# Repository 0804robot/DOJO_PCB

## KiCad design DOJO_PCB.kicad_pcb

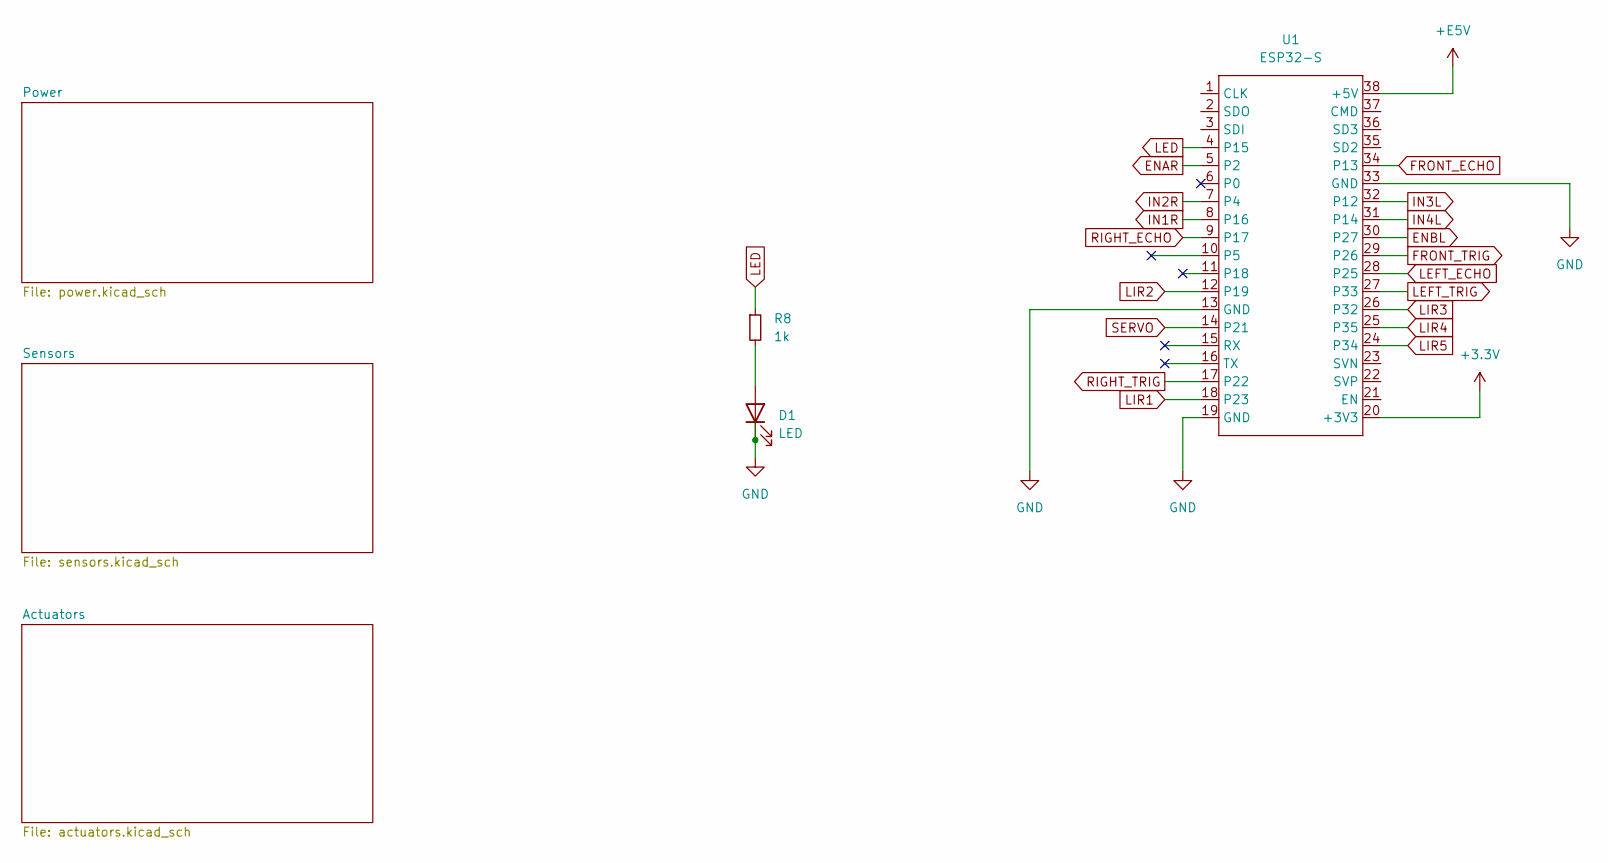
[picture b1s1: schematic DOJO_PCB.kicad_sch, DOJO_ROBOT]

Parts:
D1: LED; PinHeader_1x02_P2.54mm_Vertical
R8: 1k; R_Axial_DIN0207_L6.3mm_D2.5mm_P10.16mm_Horizontal
U1: ESP32-S

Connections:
+3.3V: U1.20 (+3V3); also elsewhere on the board
+E5V: U1.38 (+5V); also elsewhere on the board
ENAR: U1.5 (P2); also elsewhere on the board
ENBL: U1.30 (P27); also elsewhere on the board
FRONT_ECHO: U1.34 (P13); also elsewhere on the board
FRONT_TRIG: U1.29 (P26); also elsewhere on the board
GND: D1.1 (K), U1.13 (GND), U1.19 (GND), U1.33 (GND); also elsewhere on the board
IN1R: U1.8 (P16); also elsewhere on the board
IN2R: U1.7 (P4); also elsewhere on the board
IN3L: U1.32 (P12)
IN4L: U1.31 (P14)
LED: R8.1, U1.4 (P15)
LEFT_ECHO: U1.28 (P25); also elsewhere on the board
LEFT_TRIG: U1.27 (P33); also elsewhere on the board
LIR1: U1.18 (P23); also elsewhere on the board
LIR2: U1.12 (P19); also elsewhere on the board
LIR3: U1.26 (P32); also elsewhere on the board
LIR4: U1.25 (P35); also elsewhere on the board
LIR5: U1.24 (P34); also elsewhere on the board
unnamed: D1.2 (A), R8.2
RIGHT_ECHO: U1.9 (P17); also elsewhere on the board
RIGHT_TRIG: U1.17 (P22); also elsewhere on the board
SERVO: U1.14 (P21); also elsewhere on the board

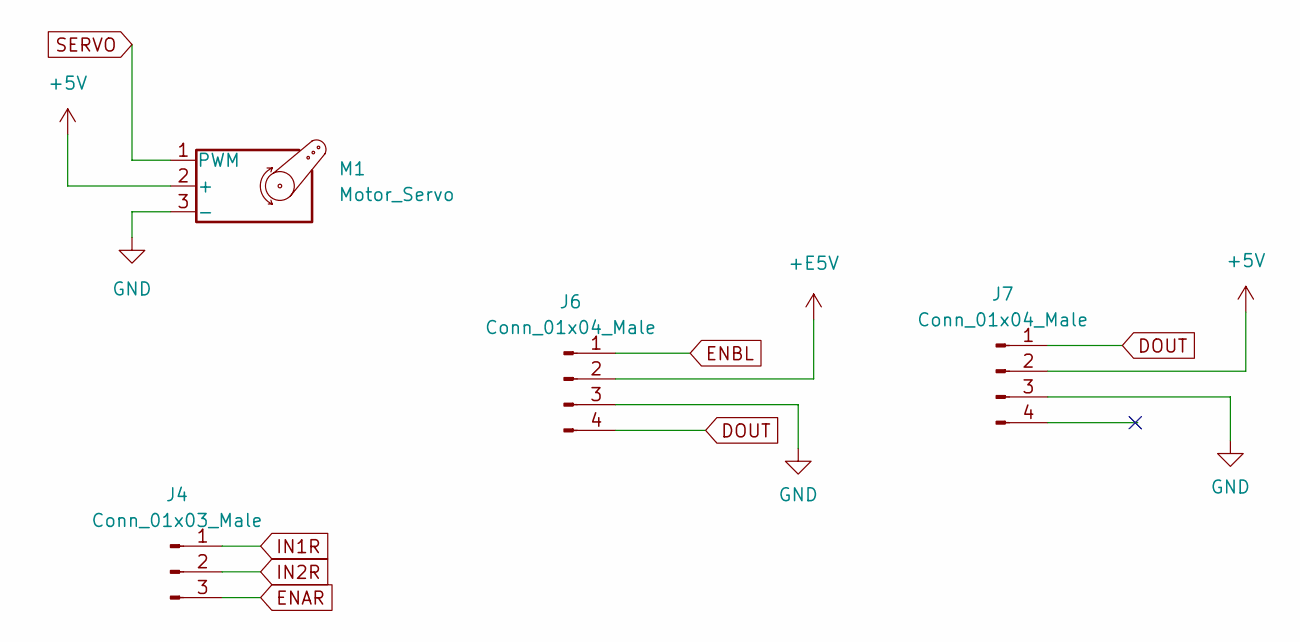
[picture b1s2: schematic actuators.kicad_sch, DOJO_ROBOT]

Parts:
J4: Conn_01x03_Male; Molex_KK-254_AE-6410-03A_1x03_P2.54mm_Vertical
J6, J7: Conn_01x04_Male; PinHeader_1x04_P2.54mm_Vertical
M1: Motor_Servo; Molex_KK-254_AE-6410-03A_1x03_P2.54mm_Vertical

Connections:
+5V: J6.2, J7.2, M1.2 (+); also elsewhere on the board
DOUT: J6.4, J7.1
ENAR: J4.3; also elsewhere on the board
ENBL: J6.1; also elsewhere on the board
GND: J6.3, J7.3, M1.3 (-); also elsewhere on the board
IN1R: J4.1; also elsewhere on the board
IN2R: J4.2; also elsewhere on the board
SERVO: M1.1 (PWM); also elsewhere on the board

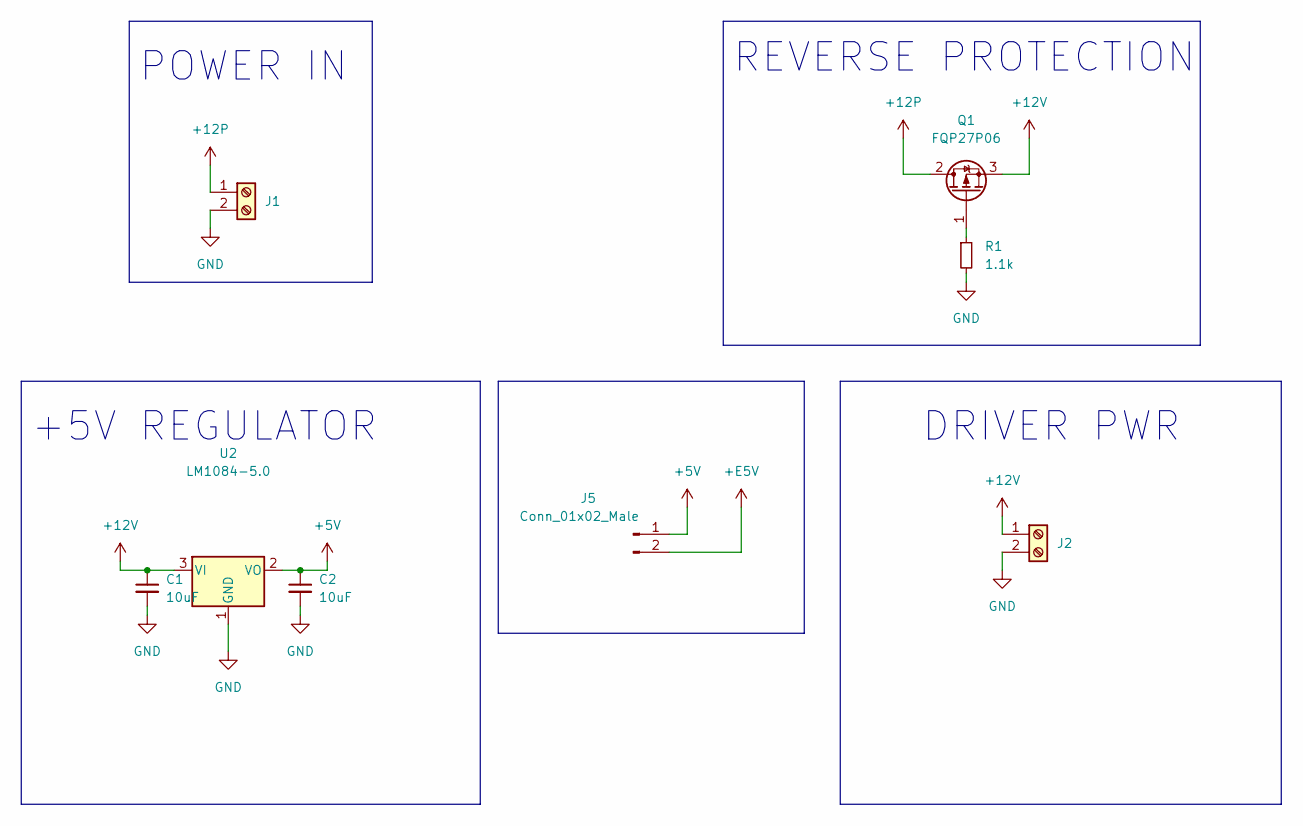
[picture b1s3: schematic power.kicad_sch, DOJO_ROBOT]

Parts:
C1, C2: 10uF; CP_Radial_D5.0mm_P2.50mm
J1, J2: Screw_Terminal_01x02; TerminalBlock_Phoenix_MKDS-1,5-2-5.08_1x02_P5.08mm_Horizont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
J5: Conn_01x02_Male; PinHeader_1x02_P2.54mm_Vertical
Q1: FQP27P06; TO-220-3_Vertical
R1: 1.1k; R_Axial_DIN0207_L6.3mm_D2.5mm_P10.16mm_Horizontal
U2: LM1084-5.0; TO-220-3_Vertical

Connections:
+5V: C2.1, J5.1, U2.2 (VO); also elsewhere on the board
+12P: J1.1, Q1.2 (D)
+12V: C1.1, J2.1, Q1.3 (S), U2.3 (VI)
+E5V: J5.2; also elsewhere on the board
GND: C1.2, C2.2, J1.2, J2.2, R1.2, U2.1 (GND); also elsewhere on the board
unnamed: Q1.1 (G), R1.1

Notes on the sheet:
+5V REGULATOR
REVERSE PROTECTION
DRIVER PWR
POWER IN

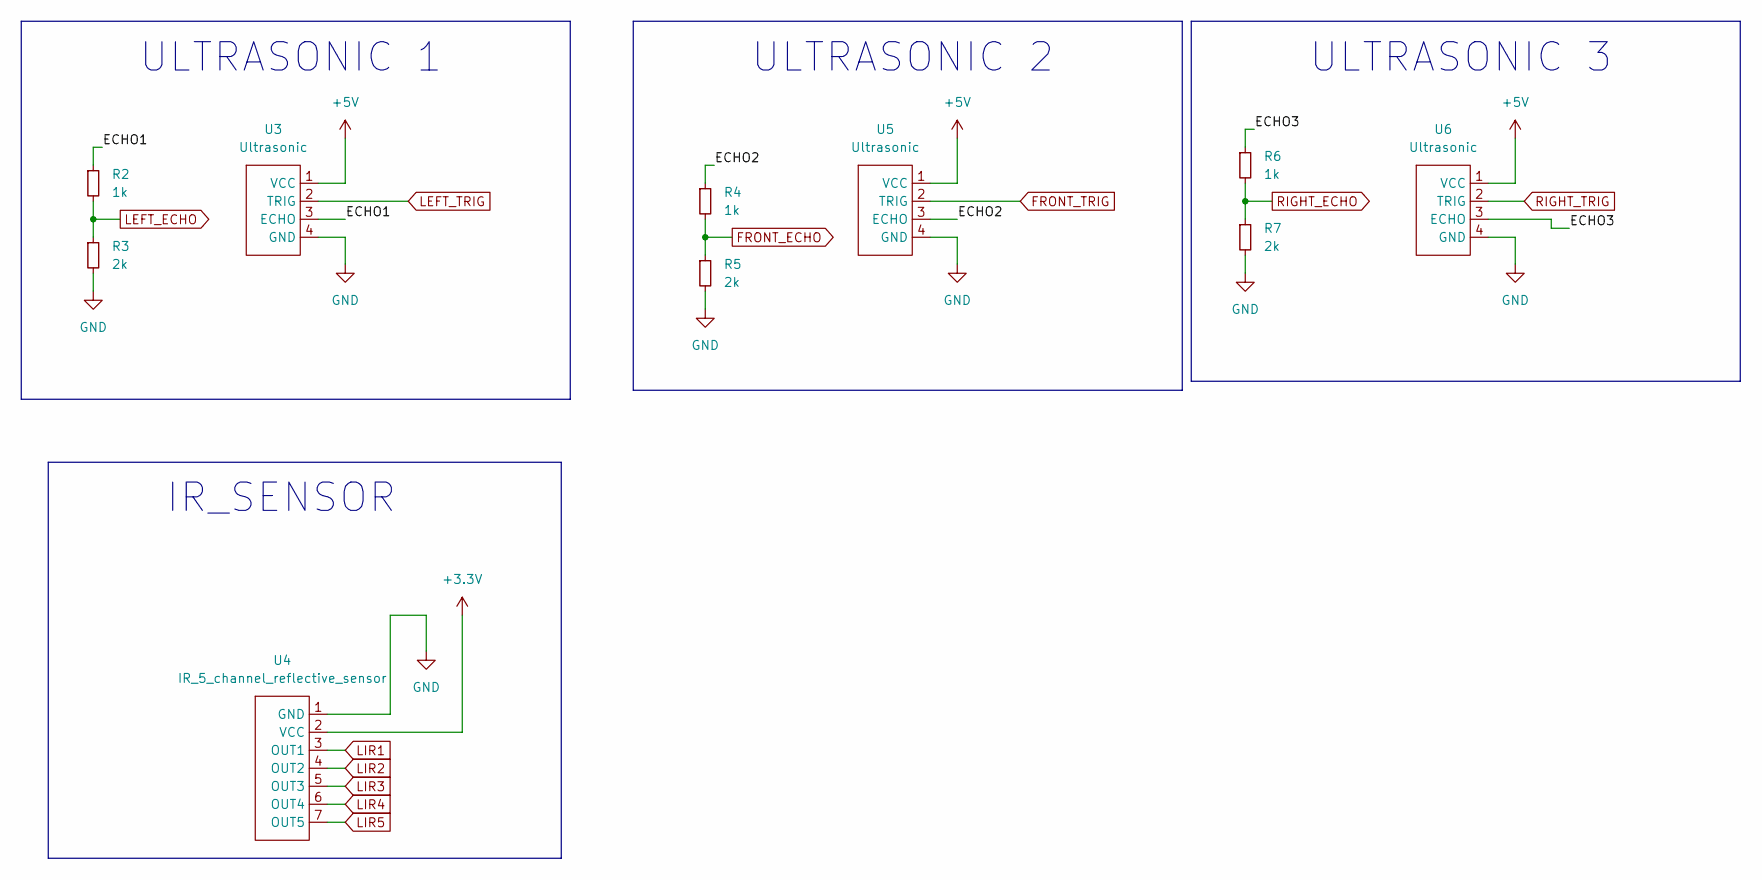
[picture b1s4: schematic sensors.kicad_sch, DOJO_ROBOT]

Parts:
R2, R4: 1k; R_Axial_DIN0207_L6.3mm_D2.5mm_P10.16mm_Horizontal
R3, R5: 2k; R_Axial_DIN0207_L6.3mm_D2.5mm_P10.16mm_Horizontal
R6: 1k; R_Axial_DIN0207_L6.3mm_D2.5mm_P15.24mm_Horizontal
R7: 2k; R_Axial_DIN0207_L6.3mm_D2.5mm_P15.24mm_Horizontal
U3, U5, U6: Ultrasonic; PinHeader_1x04_P2.54mm_Vertical
U4: IR_5_channel_reflective_sensor; PinHeader_1x07_P2.54mm_Vertical

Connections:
+3.3V: U4.2 (VCC); also elsewhere on the board
+5V: U3.1 (VCC), U5.1 (VCC), U6.1 (VCC); also elsewhere on the board
/Sensors/ECHO1: R2.1, U3.3 (ECHO)
/Sensors/ECHO2: R4.1, U5.3 (ECHO)
/Sensors/ECHO3: R6.1, U6.3 (ECHO)
FRONT_ECHO: R4.2, R5.1; also elsewhere on the board
FRONT_TRIG: U5.2 (TRIG); also elsewhere on the board
GND: R3.2, R5.2, R7.2, U3.4 (GND), U4.1 (GND), U5.4 (GND), U6.4 (GND); also elsewhere on the board
LEFT_ECHO: R2.2, R3.1; also elsewhere on the board
LEFT_TRIG: U3.2 (TRIG); also elsewhere on the board
LIR1: U4.3 (OUT1); also elsewhere on the board
LIR2: U4.4 (OUT2); also elsewhere on the board
LIR3: U4.5 (OUT3); also elsewhere on the board
LIR4: U4.6 (OUT4); also elsewhere on the board
LIR5: U4.7 (OUT5); also elsewhere on the board
RIGHT_ECHO: R6.2, R7.1; also elsewhere on the board
RIGHT_TRIG: U6.2 (TRIG); also elsewhere on the board

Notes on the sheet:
ULTRASONIC 2
ULTRASONIC 3
ULTRASONIC 1
IR_SENSOR

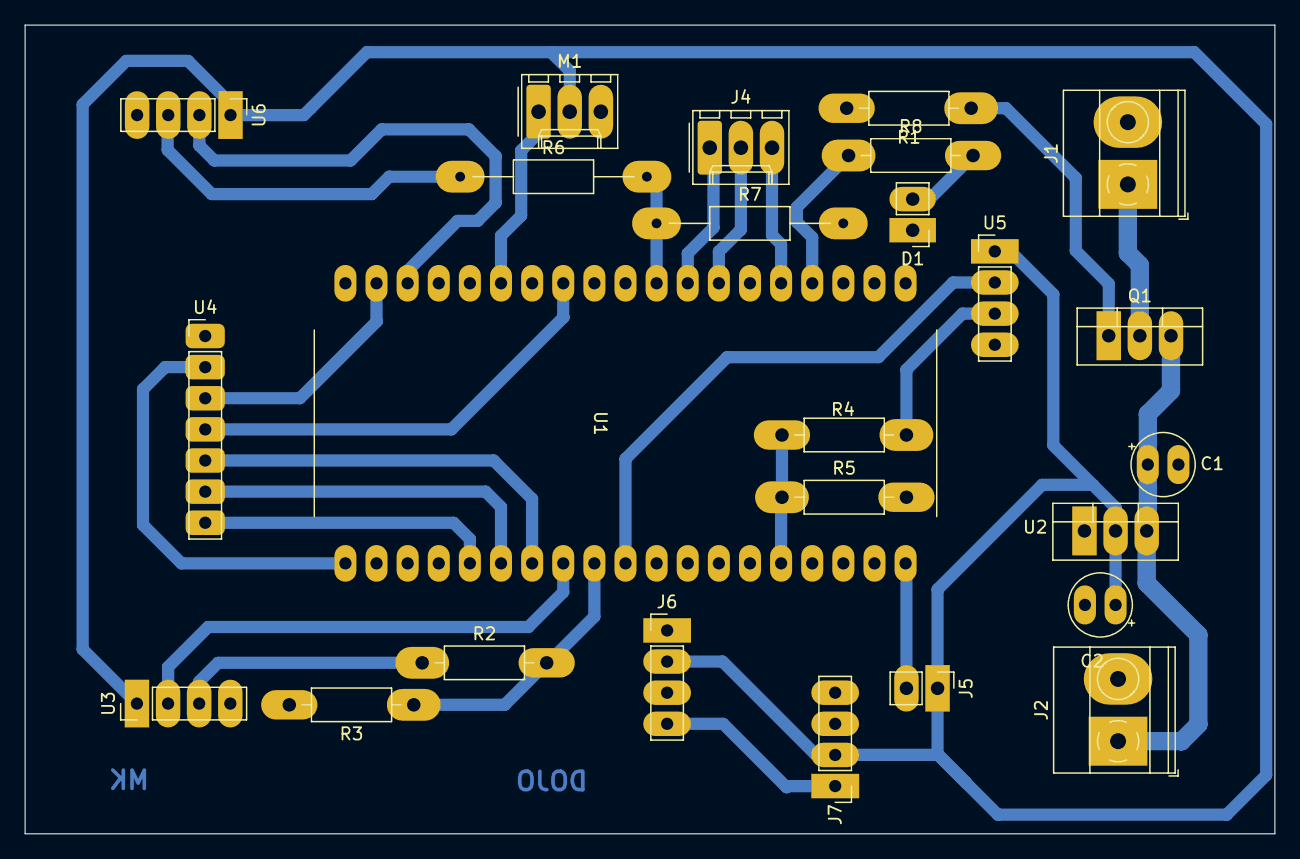
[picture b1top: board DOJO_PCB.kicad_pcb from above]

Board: 2 copper layers, 102.0 x 66.0 mm, 25 parts (0 on the bottom side), 29 nets.

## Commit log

2022-10-15 Adding readme file
2022-10-15 Adding PCB files
